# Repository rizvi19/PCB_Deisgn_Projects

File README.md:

# USB-C to UART Converter PCB

This repository contains the design files, schematics, and documentation for a custom USB-C to UART converter Printed Circuit Board (PCB). The project aims to provide a compact, reliable, and user-friendly solution for serial communication between a modern computer with a USB-C port and a microcontroller or other serial device operating at UART logic levels. The design leverages the **CP2102** USB-to-UART bridge IC, a USB-C connector, and ESD protection for robust performance.

## Features
- **USB-C Connectivity:** Modern, reversible USB-C connector supporting USB 2.0 Full Speed (12 Mbps).
- **CP2102 USB-to-UART Bridge:** Reliable single-chip solution for converting USB data to TTL-level UART signals.
- **ESD Protection:** LESD5D5.0CT1G diode array protects USB data lines from ±15 kV electrostatic discharge events.
- **Visual Feedback:** LEDs indicate power status and TX/RX data activity.
- **Compact Design:** Small form factor suitable for embedded systems development and prototyping.
- **Pin Header:** Provides easy access to UART signals (TX, RX, GND) and 3.3V power output.
- **Wide Baud Rate Support:** Configurable baud rates (e.g., 9600, 115200 bps) for compatibility with various microcontrollers.
- **Open-Source:** All design files (schematics, PCB layout, BOM) are available in this repository.

## Repository Contents
- `/schematics`: KiCad schematic files for the USB-C to UART converter.
- `/pcb`: KiCad PCB layout files and Gerber files for manufacturing.
- `/3d_models`: 3D visualization files of the assembled PCB.
- `/docs`: Project documentation, including the detailed design report (`USB-C_to_UART_Converter_Report.pdf`).
- `/bom`: Bill of Materials (BOM) listing all components with part numbers and suppliers.

## Hardware Overview
The PCB integrates the following key components:
- **CP2102:** Converts USB data to UART signals, enumerates as a Virtual COM Port (VCP) on the host computer.
- **USB-C Receptacle:** Provides a modern interface with VBUS (5V), GND, and USB 2.0 data lines (D+, D-).
- **LESD5D5.0CT1G:** ESD protection for USB data lines to enhance durability.
- **LEDs and Resistors:** Power LED (3.3V) and activity LED (TX/RX) with current-limiting resistors (330 Ω).
- **Capacitors:** Decoupling capacitors (0.1 µF, 1 µF, 4.7 µF) for power stability.
- **Pin Header:** 4-pin header for TX, RX, GND, and 3.3V output.

## User Manual
### Prerequisites
- A computer with a USB-C port and drivers for the CP2102 (available from [Silicon Labs](https://www.silabs.com/interface/usb-bridges/classic/device.cp2102)).
- A microcontroller or serial device with UART interface (3.3V or 5V logic levels).
- Jumper wires or a compatible connector for the pin header.
- Terminal software (e.g., PuTTY, Tera Term, or Arduino Serial Monitor) for serial communication.

### Setup Instructions
1. **Driver Installation:**
   - Download and install the CP2102 VCP drivers from [Silicon Labs](https://www.silabs.com/interface/usb-bridges/classic/device.cp2102).
   - Upon connecting the PCB to your computer via a USB-C cable, it should enumerate as a COM port (e.g., COM3 on Windows or `/dev/ttyUSB0` on Linux).

2. **Connecting to a Microcontroller:**
   - Connect the PCB’s pin header to your microcontroller:
     - **TX (PCB)** → **RX (Microcontroller)**
     - **RX (PCB)** → **TX (Microcontroller)**
     - **GND (PCB)** → **GND (Microcontroller)**
     - (Optional) **3.3V (PCB)** → Power input for the microcontroller (if needed, ensure current draw < 100 mA).
   - Use jumper wires or a compatible connector for secure connections.

3. **Configuring the Serial Port:**
   - Open your terminal software and select the appropriate COM port.
   - Set the baud rate to match your microcontroller (e.g., 9600, 115200 bps).
   - Configure other settings (typically 8 data bits, no parity, 1 stop bit, no flow control).

4. **Testing Communication:**
   - Power on the microcontroller and send data (e.g., via a simple `Serial.print()` in Arduino).
   - The activity LED on the PCB should blink during data transfer.
   - Verify that data appears in the terminal software and vice versa.

### LED Indicators
- **Power LED:** Lights up when the PCB is powered via USB (indicates 3.3V regulator is active).
- **Activity LED:** Blinks during TX or RX data transfers, providing visual feedback of serial communication.

### Troubleshooting
- **No COM Port Detected:** Ensure the CP2102 drivers are installed and the USB-C cable is functional (try a different cable/port).
- **No Data Transfer:** Verify TX/RX connections are correct (not swapped) and the baud rate matches on both devices.
- **LED Not Lighting:** Check USB power and connections; ensure the LED resistors are properly soldered.
- **Unstable Operation:** Inspect solder joints and verify that decoupling capacitors are correctly placed.

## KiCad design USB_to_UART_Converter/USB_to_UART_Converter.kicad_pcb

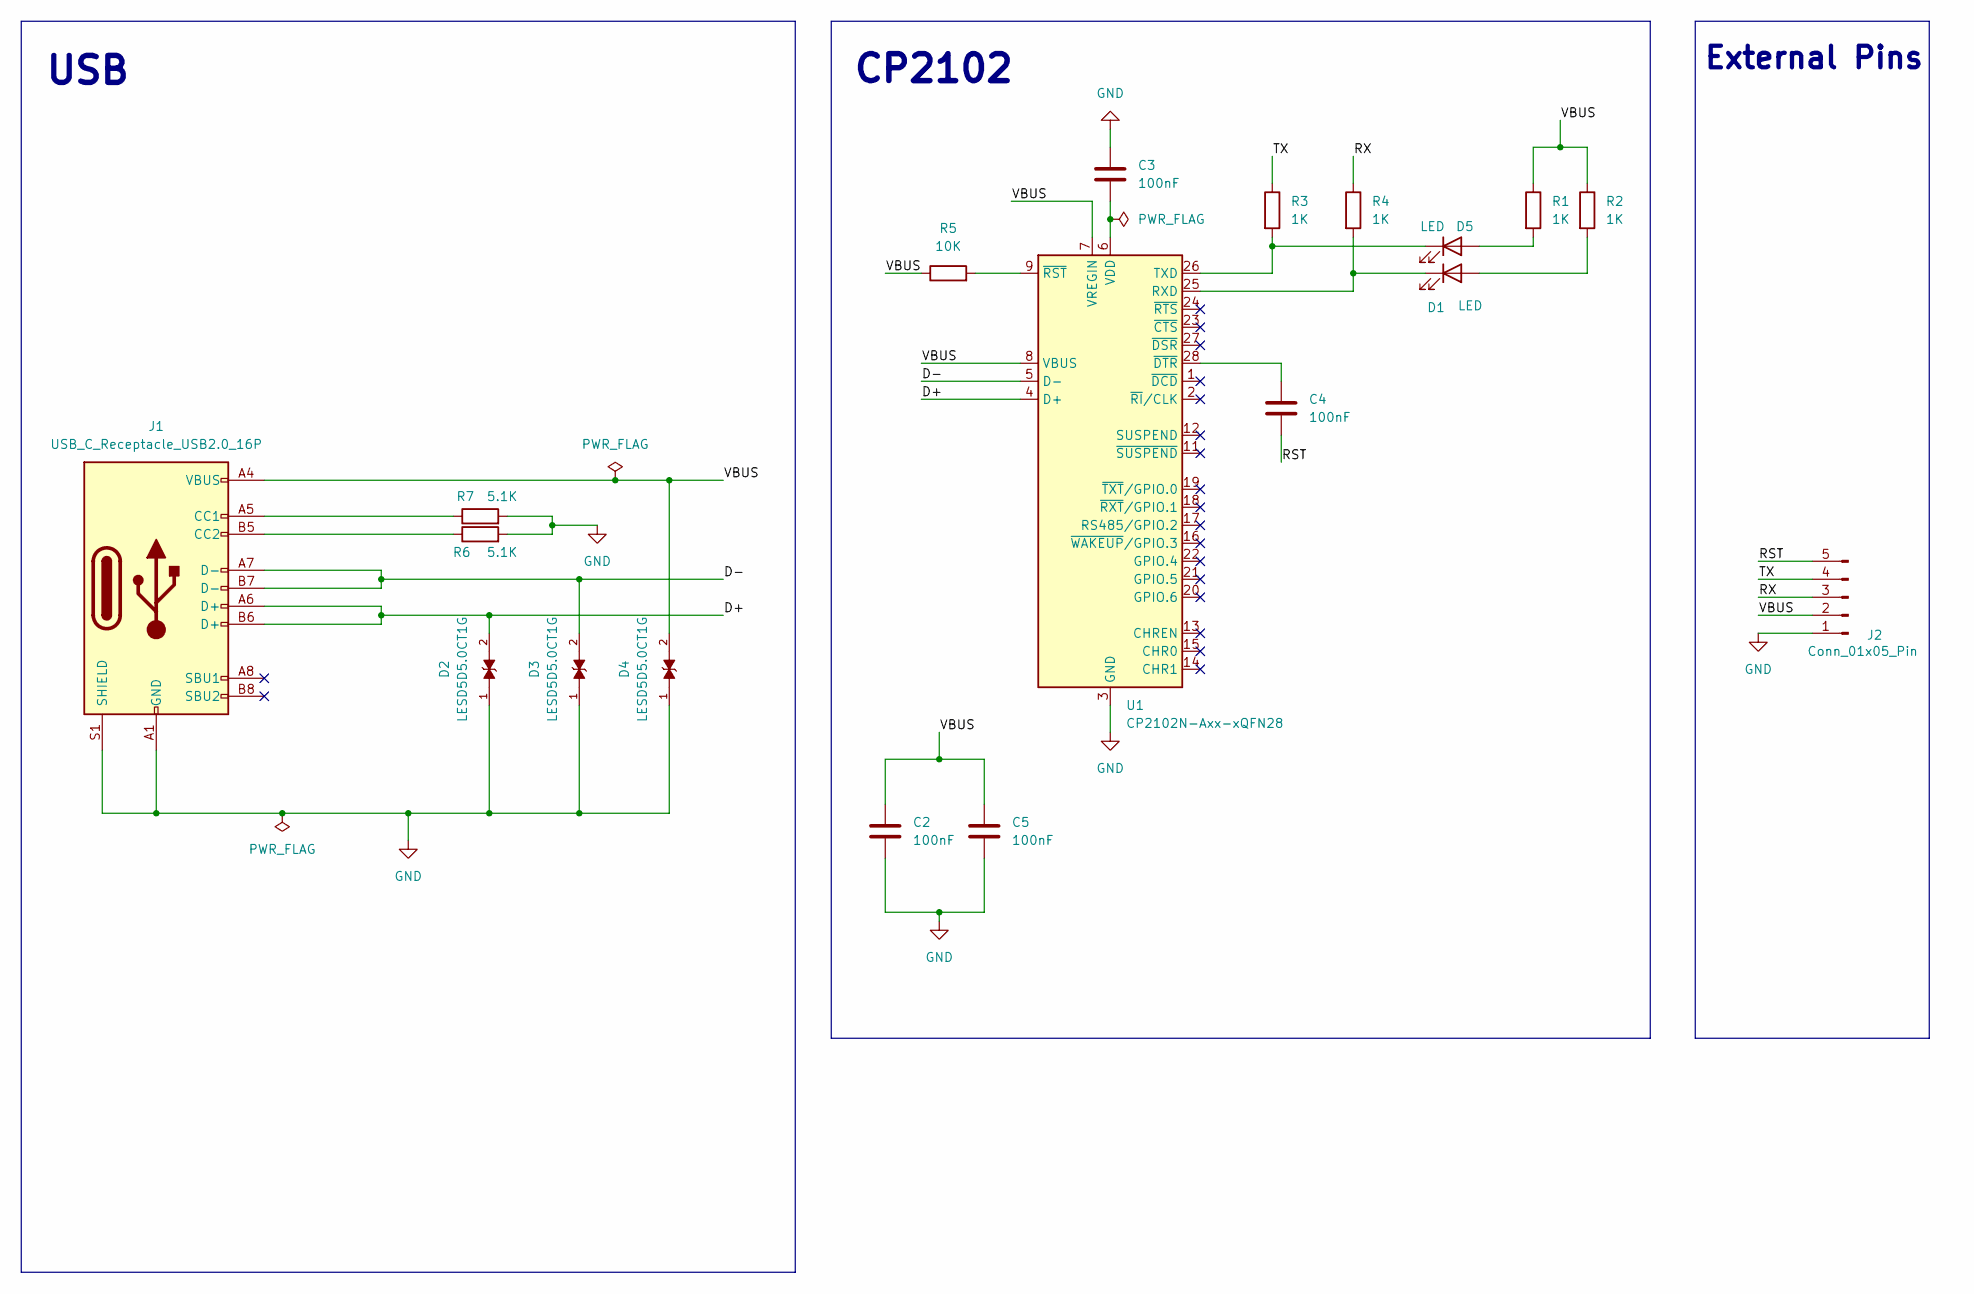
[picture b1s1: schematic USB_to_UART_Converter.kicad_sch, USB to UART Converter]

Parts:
C2, C3, C4, C5: 100nF; C_0201_0603Metric
D1, D5: LED; LED_0201_0603Metric
D2, D3, D4: LESD5D5.0CT1G; TVS_LESD5D5.0CT1G; PARTREV O
J1: USB_C_Receptacle_USB2.0_16P; USB_C_Receptacle_HRO_TYPE-C-31-M-12
J2: Conn_01x05_Pin; PinHeader_1x05_P2.54mm_Horizontal
R1, R2, R3, R4: 1K; R_0201_0603Metric
R5: 10K; R_0201_0603Metric
R6, R7: 5.1K; R_0201_0603Metric
U1: CP2102N-Axx-xQFN28; QFN-28-1EP_5x5mm_P0.5mm_EP3.35x3.35mm

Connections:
/D+: D2.2, J1.A6 (D+), J1.B6 (D+), U1.4 (D+)
/D-: D3.2, J1.A7 (D-), J1.B7 (D-), U1.5 (D-)
/RST: C4.2, J2.5
/RX: J2.3, R4.1
/TX: J2.4, R3.1
/VBUS: C2.1, C5.1, D4.2, J1.A4 (VBUS), J1.A9 (VBUS), J1.B4 (VBUS), J1.B9 (VBUS), J2.2, R1.1, R2.1, R5.1, U1.7 (VREGIN), U1.8 (VBUS)
GND: C2.2, C3.1, C5.2, D2.1, D3.1, D4.1, J1.A1 (GND), J1.A12 (GND), J1.B1 (GND), J1.B12 (GND), J1.S1 (SHIELD), J2.1, R6.2, R7.2, U1.3 (GND), U1.29 (GND)
unnamed: D1.2 (A), R2.2
unnamed: D1.1 (K), R4.2, U1.25 (RXD)
unnamed: D5.2 (A), R1.2
unnamed: D5.1 (K), R3.2, U1.26 (TXD)
unnamed: J1.A5 (CC1), R7.1
unnamed: J1.B5 (CC2), R6.1
unnamed: C3.2, U1.6 (VDD)
unnamed: C4.1, U1.28 (~DTR)
unnamed: R5.2, U1.9 (~RST)

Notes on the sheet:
USB
External Pins
CP2102

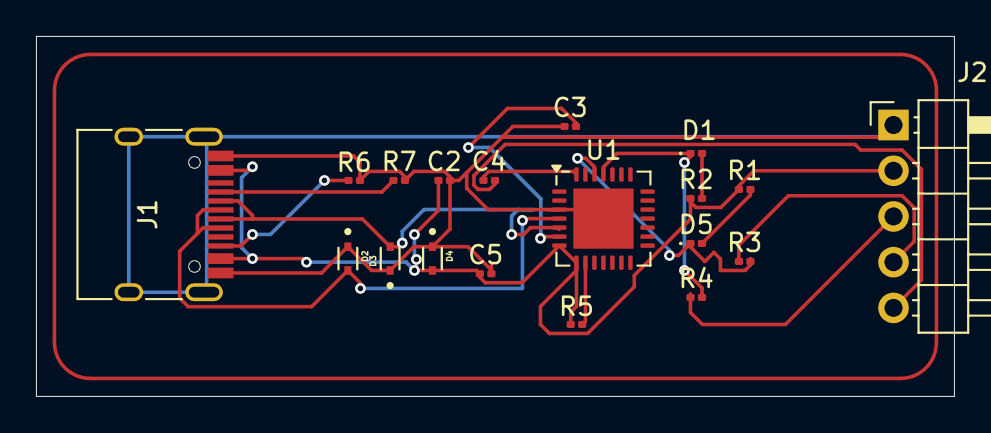
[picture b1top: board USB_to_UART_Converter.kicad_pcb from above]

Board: 2 copper layers, 51.0 x 20.0 mm, 19 parts (0 on the bottom side), 16 nets.

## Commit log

2025-07-07 Final Up
